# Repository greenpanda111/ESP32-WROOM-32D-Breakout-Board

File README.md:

# ESP32-WROOM-32D HW-394 Breakout-Board

This repo contains the symbol, footprint, and breakout board files for the ESP32 HW-394 (Commonly found on AliExpress)

The breakout board has 5 extra pins for 5V, 3V3, and GND each

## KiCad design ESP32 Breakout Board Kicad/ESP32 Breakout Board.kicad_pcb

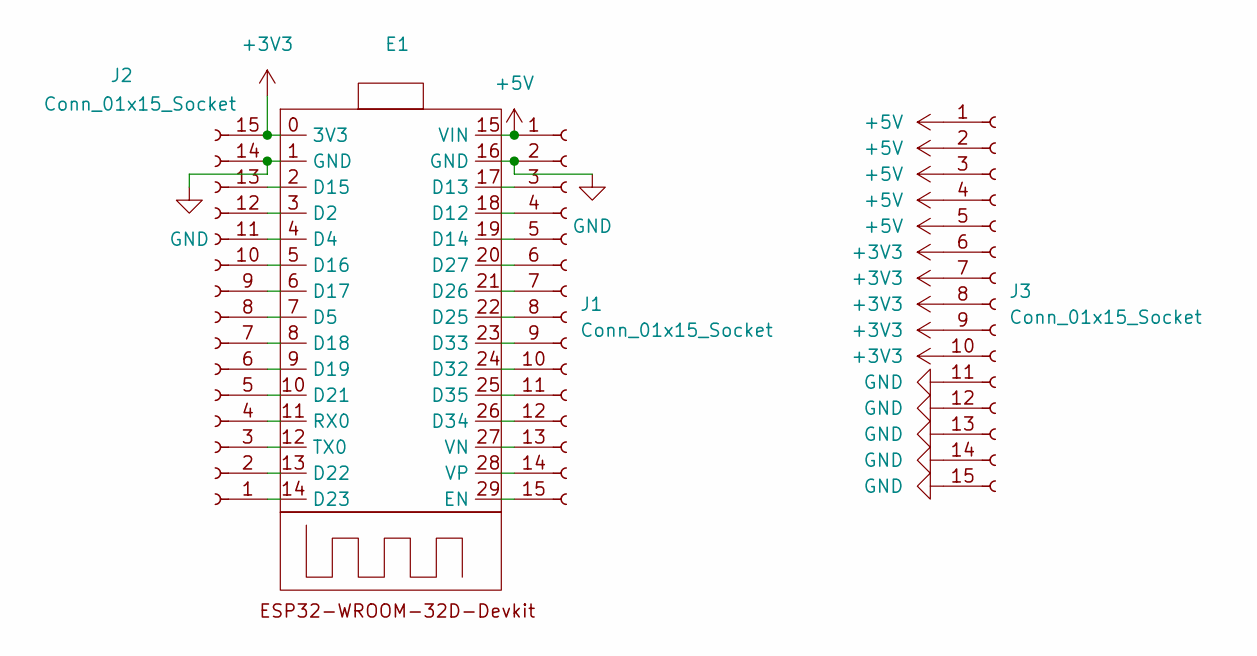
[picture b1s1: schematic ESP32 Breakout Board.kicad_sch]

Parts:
E1: ESP32-WROOM-32D-Devkit
J1, J2, J3: Conn_01x15_Socket; PinSocket_1x15_P2.54mm_Vertical

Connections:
+3V3: E1.0 (3V3), J2.15, J3.6, J3.7, J3.8, J3.9, J3.10
+5V: E1.15 (VIN), J1.1, J3.1, J3.2, J3.3, J3.4, J3.5
GND: E1.1 (GND), E1.16 (GND), J1.2, J2.14, J3.11, J3.12, J3.13, J3.14, J3.15
unnamed: E1.3 (D2), J2.12
unnamed: E1.4 (D4), J2.11
unnamed: E1.7 (D5), J2.8
unnamed: E1.18 (D12), J1.4
unnamed: E1.17 (D13), J1.3
unnamed: E1.19 (D14), J1.5
unnamed: E1.2 (D15), J2.13
unnamed: E1.5 (D16), J2.10
unnamed: E1.6 (D17), J2.9
unnamed: E1.8 (D18), J2.7
unnamed: E1.9 (D19), J2.6
unnamed: E1.10 (D21), J2.5
unnamed: E1.13 (D22), J2.2
unnamed: E1.14 (D23), J2.1
unnamed: E1.22 (D25), J1.8
unnamed: E1.21 (D26), J1.7
unnamed: E1.20 (D27), J1.6
unnamed: E1.24 (D32), J1.10
unnamed: E1.23 (D33), J1.9
unnamed: E1.26 (D34), J1.12
unnamed: E1.25 (D35), J1.11
unnamed: E1.29 (EN), J1.15
unnamed: E1.11 (RX0), J2.4
unnamed: E1.12 (TX0), J2.3
unnamed: E1.27 (VN), J1.13
unnamed: E1.28 (VP), J1.14

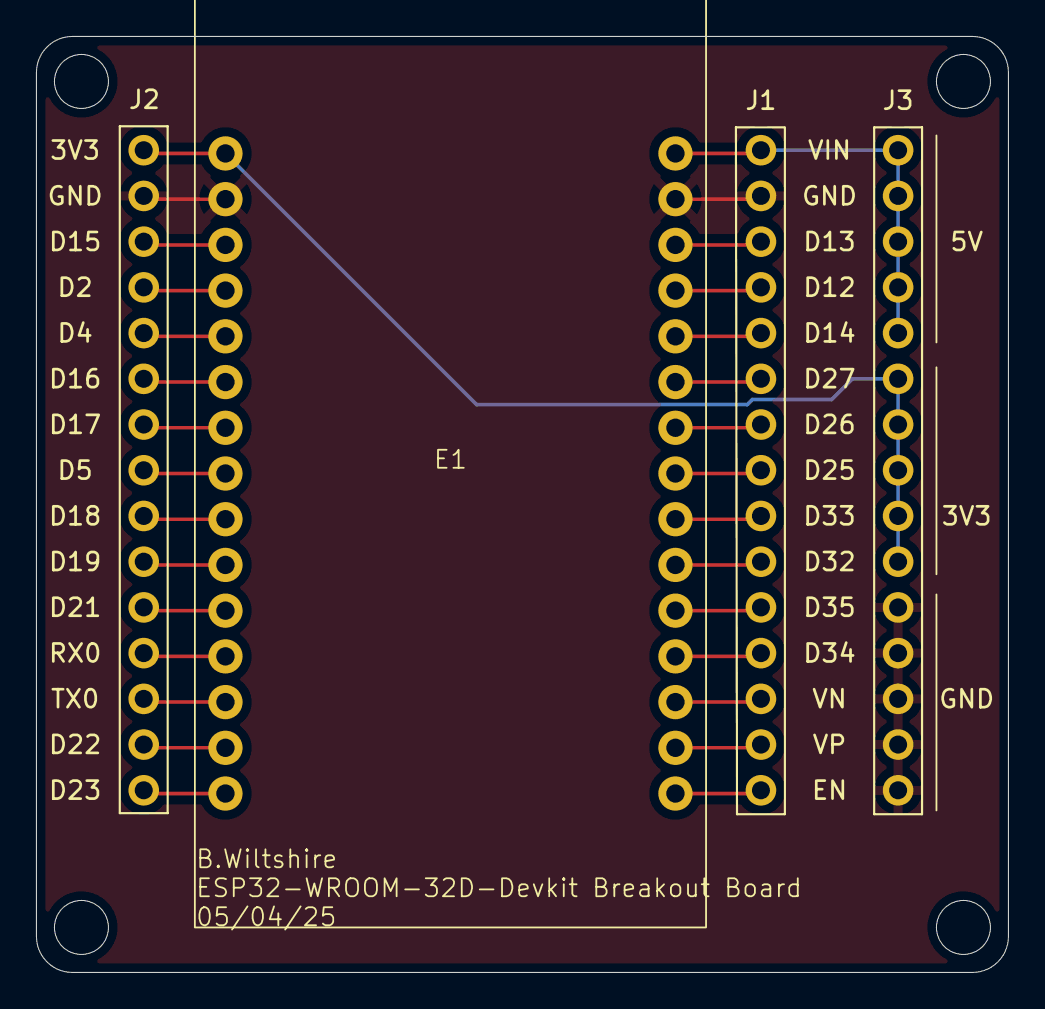
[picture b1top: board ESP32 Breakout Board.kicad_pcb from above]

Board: 2 copper layers, 54.0 x 52.0 mm, 4 parts (0 on the bottom side), 29 nets.

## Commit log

2025-04-05 Kicad files uploaded
2025-04-05 Image Added
2025-04-05 Folder renamed
2025-04-05 Footprint and Symbol Added
2025-04-05 git ignore added
2025-04-05 Filleted Image added
2025-04-05 Updated gitignore
2025-04-05 git ignore updated
2025-04-05 git ignore implemented
2025-04-06 Exports
